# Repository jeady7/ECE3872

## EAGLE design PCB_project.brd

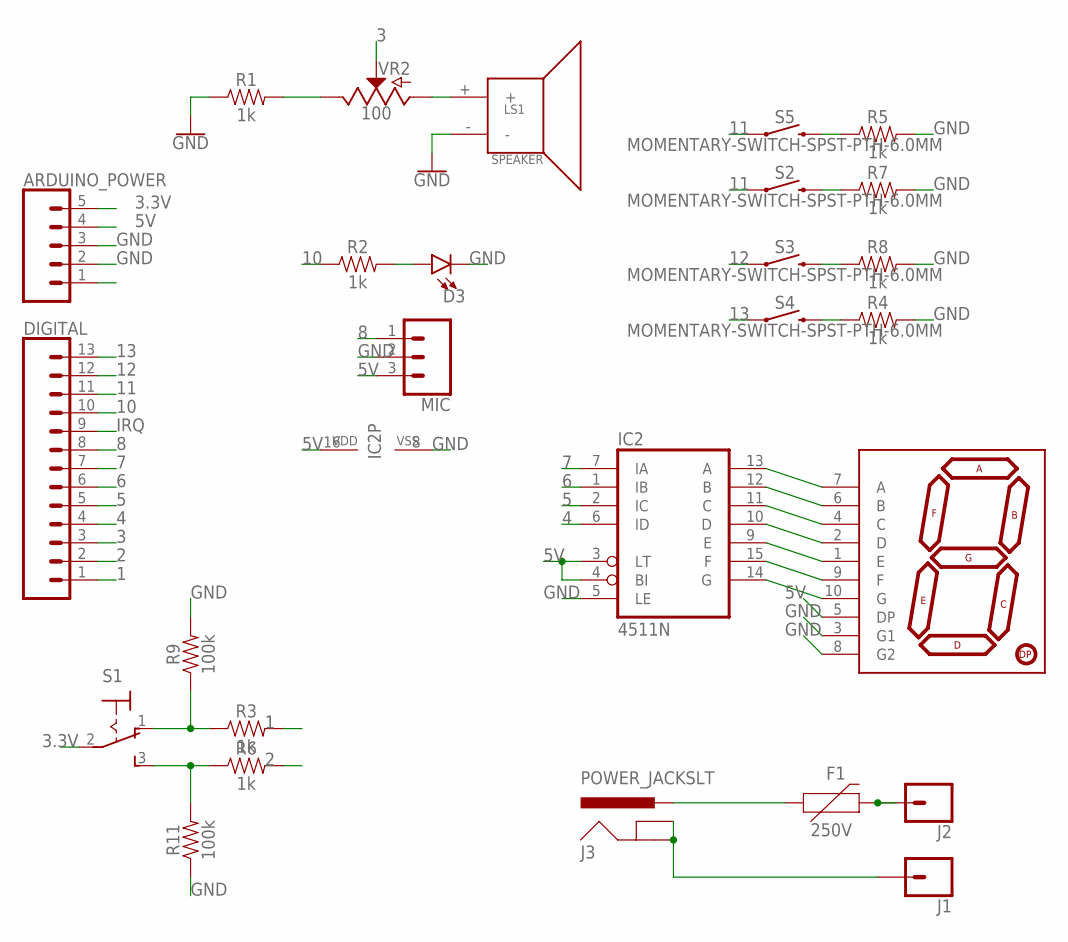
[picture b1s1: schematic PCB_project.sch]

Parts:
ARDUINO_POWER: CONN_05; 1X05
D3: LED-3MM-NO_SILK; LED_3MM-NS
DIGITAL: CONN_13; 1X13
F1: 250V; 1206
IC2: 4511N; DIL16
J1, J2: CONN_01; 1X01
J3: POWER_JACKSLT; POWER_JACK_SLOT
LS1: SPEAKER; PCB_MOUNT_SPEAKER
MIC: CONN_03; 1X03
R1, R2, R3, R4, R5, R6, R7, R8: 1k; AXIAL-0.3
R9, R11: 100k; AXIAL-0.3
S1: 320-916
S2, S3, S4, S5: MOMENTARY-SWITCH-SPST-PTH-6.0MM; TACTILE_SWITCH_PTH_6.0MM
U$1: YSD-160AB3C-8; 7-SEGMENT-1"PTH
VR2: 100; POT-PTH-ALPS

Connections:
1: DIGITAL.1, R3.P$2 (2)
2: DIGITAL.2, R6.P$2 (2)
3: DIGITAL.3, VR2.P$2 (S)
3.3V: ARDUINO_POWER.5, S1.2
4: DIGITAL.4, IC2.6 (ID)
5: DIGITAL.5, IC2.2 (IC)
5V: ARDUINO_POWER.4, IC2.3 (LT), IC2.4 (BI), IC2.16 (VDD), MIC.3, U$1.5 (DP)
6: DIGITAL.6, IC2.1 (IB)
7: DIGITAL.7, IC2.7 (IA)
8: DIGITAL.8, MIC.1
10: DIGITAL.10, R2.P$1 (1)
11: DIGITAL.11, S2.1, S5.1
12: DIGITAL.12, S3.1
13: DIGITAL.13, S4.1
GND: ARDUINO_POWER.2, ARDUINO_POWER.3, D3.K (C), IC2.5 (LE), IC2.8 (VSS), LS1.-, MIC.2, R1.P$1 (1), R4.P$2 (2), R5.P$2 (2), R7.P$2 (2), R8.P$2 (2), R9.P$2 (2), R11.P$1 (1), U$1.3 (G1), U$1.8 (G2)
IRQ: DIGITAL.9
unnamed: LS1.+, VR2.P$3 (A)
unnamed: D3.A, R2.P$2 (2)
unnamed: IC2.13 (A), U$1.7 (A)
unnamed: IC2.12 (B), U$1.6 (B)
unnamed: IC2.11 (C), U$1.4 (C)
unnamed: IC2.10 (D), U$1.2 (D)
unnamed: IC2.9 (E), U$1.1 (E)
unnamed: IC2.15 (F), U$1.9 (F)
unnamed: IC2.14 (G), U$1.10 (G)
unnamed: R1.P$2 (2), VR2.P$1 (E)
unnamed: R3.P$1 (1), R9.P$1 (1), S1.1 (O)
unnamed: R4.P$1 (1), S4.3 (2)
unnamed: J1.1, J3.GND@1 (GNDBREAK), J3.GND@2 (GND)
unnamed: R6.P$1 (1), R11.P$2 (2), S1.3 (S)
unnamed: R7.P$1 (1), S2.3 (2)
unnamed: R8.P$1 (1), S3.3 (2)
unnamed: F1.1, J3.PWR
unnamed: R5.P$1 (1), S5.3 (2)
unnamed: F1.2, J2.1

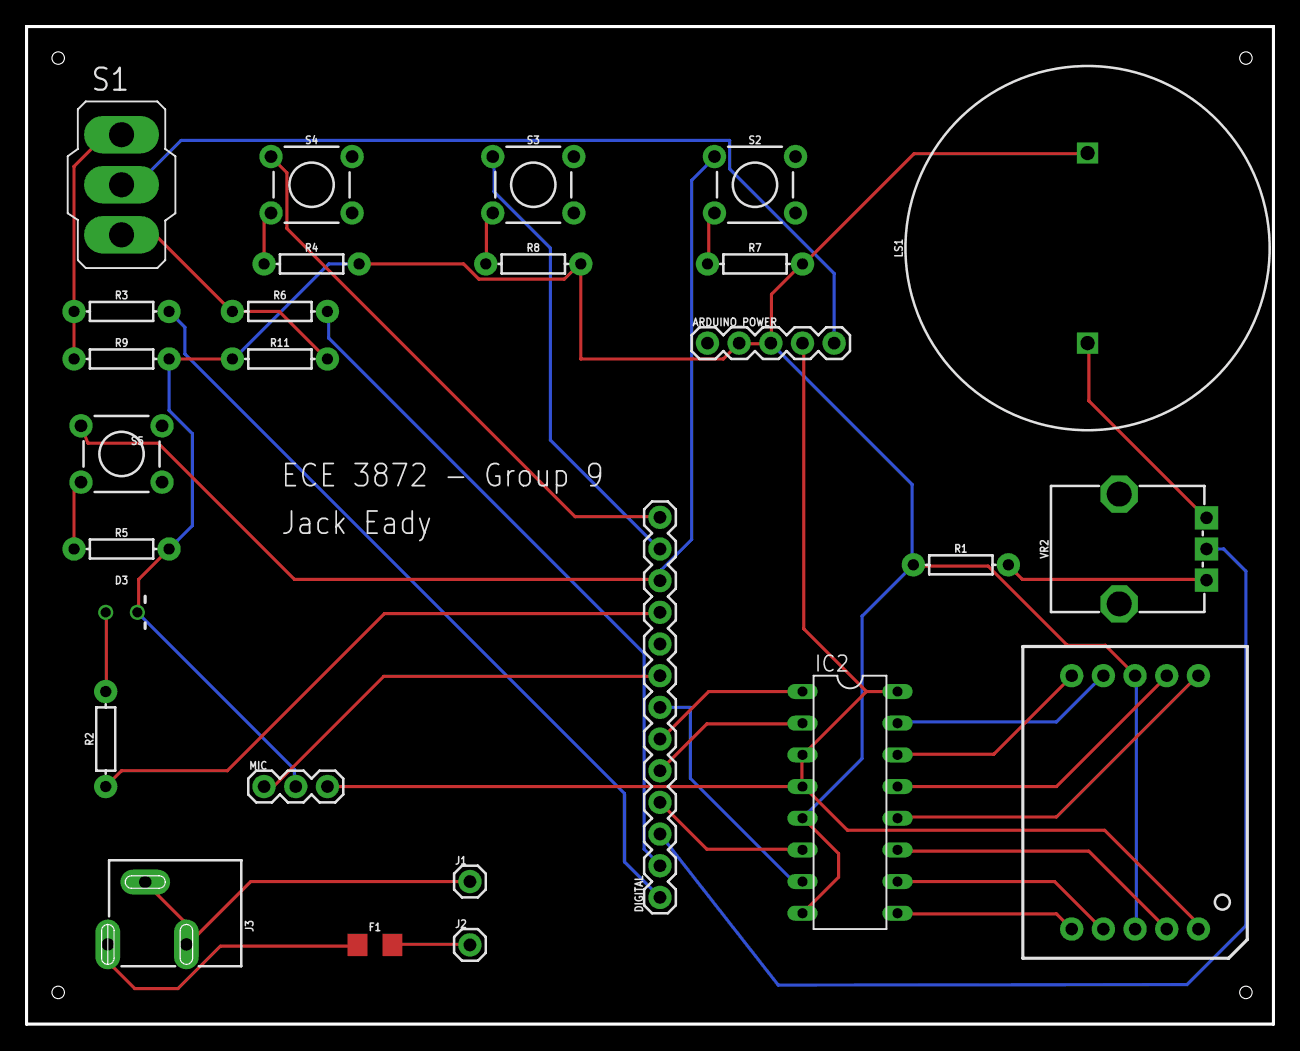
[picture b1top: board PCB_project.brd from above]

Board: 2 copper layers, 100.0 x 80.0 mm, 27 parts (0 on the bottom side), 34 nets.

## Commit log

2021-09-22 Add files via upload
    Touchpad
2021-10-12 Created initial Skeleton code
    Implemented basic state machine functionality
2021-11-07 Add files via upload
    Integreated Code with no servos and mandatory skip first listen

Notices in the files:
parts and their libraries:
SparkFun-Connectors: Licensing: Creative Commons ShareAlike 4.0 International - https://creativecommons.org/licenses/by-sa/4.0
